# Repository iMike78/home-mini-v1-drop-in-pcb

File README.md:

# MiciMike drop-in PCB replacement for Google Home Mini (Gen 1)

[MiciMike Home Mini](https://github.com/iMike78/home-mini-v1-drop-in-pcb) is a drop-in PCB replacement for the original [Google Home Mini](https://en.wikipedia.org/wiki/Google_Nest_(smart_speakers)) with the Micro-USB power connector. It replaces the original electronics with open-source hardware based on an ESP32-S3 and an XMOS xCORE audio processor, and is intended to run ESPHome-based open voice assistant firmware.

The project follows the Home Assistant Voice Preview Edition architecture as closely as the Google Home Mini enclosure allows, while adapting the layout, connectors, controls, microphones, LEDs, and audio path to the original speaker shell.

## Current Status

- Schematic completed
- Component placement completed
- Routing completed
- Ground pour, shielding, and EMI strategy completed
- First prototype batch tested
- Validation batch received and under test
- ESPHome factory provisioning validated with BLE Improv and Home Assistant discovery

## Update: v0.9.5 Touch Controller Migration and Test Points

### Touch Controller Change

The ESP32-S3 built-in touch peripheral has been replaced with an external **MPR121 capacitive touch controller** on the I2C bus at address `0x5A`. This avoids an unresolved ESP-IDF / hardware issue (`IDFGH-16448`) where the touch sensor FSM could lock up and leave all channels stuck at their maximum raw value.

What changed:

- **Hardware:** MPR121 added on the clean `+3V3` rail. Touch pads connect through `ELEC0` to `ELEC2`; IRQ is on `GPIO2`. Unused electrodes are tied together to GND through a single 1 Mohm resistor.
- **Firmware:** the ESPHome `esp32_touch` component was removed and replaced with an `mpr121` hub plus three binary sensors for `volume_down`, `center_button`, and `volume_up`.
- **Freed pins:** ESP32-S3 `GPIO3` and `GPIO4` are no longer used for capacitive touch.

The center touch button is also used as the BLE Improv authorizer in the factory firmware, matching the Home Assistant Voice PE provisioning flow.

### New Solderable Test Points

The board exposes large, easy-to-solder test points for users who do not have the original Google Home Mini daughterboard and FPC connector, or who want to integrate the PCB into a custom enclosure.

- **+5V and GND power input pads:** allow direct power injection without using the original FPC connector.
- **Mute switch pad:** exposes the hardware mute input, which has an on-board pull-up. Pull this pad to GND to power the microphones; otherwise the board remains muted and the microphone path is disabled.

## ESPHome Firmware

The ESPHome configuration lives in [esphome/](./esphome/):

- [micimike-factory.yml](./esphome/micimike-factory.yml) is the manufacturing / first-install firmware. It mirrors the Home Assistant Voice PE factory flow: BLE Improv provisioning, center-button authorization, Home Assistant discovery, and the full voice firmware configuration included underneath.
- [micimike-voice.yml](./esphome/micimike-voice.yml) is the full voice assistant firmware configuration used by the factory build and by normal ESPHome installs.

Typical factory flashing:

```bash
esphome run esphome/micimike-factory.yml
```

After flashing, Home Assistant should discover the device via BLE Improv, ask for Wi-Fi credentials, request center-button authorization, and then add the ESPHome device. The fallback Wi-Fi AP is present, but no captive portal or web server is intentionally enabled.

## Crowdfunding

The crowdfunding campaign is live on Crowd Supply in its pre-order phase. You can subscribe there to show interest and receive email updates:

https://www.crowdsupply.com/micimike-rev-devices/micimike-home-mini-drop-in-pcb

If you are looking for a similar drop-in PCB replacement for the Google Nest Mini, see the sister project:

https://github.com/iMike78/nest-mini-drop-in-pcb

## Project Scope

This repository and its sister project are open-source hardware projects inspired in part by [Onju Voice](https://github.com/justLV/onju-voice), but designed around the open voice assistant hardware direction established by the Open Home Foundation and Home Assistant Voice Preview Edition.

The primary target audience is people who want to repurpose Google Home Mini and Google Nest Mini speakers into open-source Home Assistant voice assistant hardware and/or media player speaker output for [Music Assistant](https://www.music-assistant.io). The hardware may also be useful for other ESP32-based firmware projects.

The design integrates:

- ESP32-S3 for Wi-Fi, BLE, ESPHome, and onboard wake-word detection
- XMOS xCORE XU316 for advanced audio processing
- Local audio cleanup support for noise suppression, acoustic echo cancellation, interference cancellation, and automatic gain control

Functionally, the goal is to stay as compatible as practical with the [Home Assistant Voice Preview Edition](https://www.home-assistant.io/blog/2024/12/19/voice-preview-edition-the-era-of-open-voice/) reference design. The main differences come from the tight mechanical constraints of the Google Home Mini enclosure and original components.

This repository is not intended to become a separate upstream for new ESPHome or XMOS voice features. Feature development should generally happen upstream:

- https://github.com/esphome/home-assistant-voice-pe
- https://github.com/esphome/esphome
- https://github.com/esphome/voice-kit-xmos-firmware

## Collaboration and Contributions

If you would like to support the project, you can buy me a coffee via Ko-fi:

https://ko-fi.com/imike78

Contributions are especially welcome from people with board-level electrical design, KiCad layout, PCB routing, ground-pour strategy, EMI, and mixed-signal audio layout experience. Please open an issue, join an existing discussion, or start a new discussion in this repository.

Background discussion on the Home Assistant community forum:

https://community.home-assistant.io/t/any-news-on-alternative-to-onju-voice-pcb-repacement-design-for-google-nest-home-mini-speakers-with-added-xmos-chip-to-match-official-home-assistant-voice-preview-edition-reference-hardware/860001/

## Tools Used

- KiCad 9
- SnapEDA / LCSC for footprint sourcing

## Known Hardware Specifications

- 4-layer PCB
- ESP32-S3R8 bare chip with 16MB flash
- XMOS XU316-1024-QF60B-C24 xCORE DSP audio processor with 4MB flash
- Dual I2S buses for simultaneous audio input and output
- AIC3204 DAC and TPA6211 power amplifier for speaker output
- 2x T3902 MEMS microphones with 68mm spacing
- 4x SK6812 RGB LEDs
- MPR121 capacitive touch controller

## References

### Home Assistant Voice Preview Edition

- https://www.home-assistant.io/blog/2024/12/19/voice-preview-edition-the-era-of-open-voice/
- https://voice-pe.home-assistant.io/resources/
- https://support.nabucasa.com/hc/en-us/categories/24451727188125-Home-Assistant-Voice-Preview-Edition
- https://github.com/esphome/home-assistant-voice-pe
- https://esphome.github.io/home-assistant-voice-pe/

### XMOS xCORE DSP

- https://www.xmos.com/download/XU316-1024-QF60B-xcore.ai-Datasheet(3).pdf
- https://www.xmos.com/software-tools/
- https://www.xmos.com/develop/xcore-voice
- https://www.xmos.com/usb-multichannel-audio/
- https://www.xmos.com/xcore-ai

### XMOS Firmware

- https://github.com/esphome/voice-kit-xmos-firmware
- https://github.com/esphome/xmos_fwk_rtos
- https://github.com/esphome/xmos_fwk_io

## License

This project is licensed under the [CERN Open Hardware License Version 2 - Strongly Reciprocal (CERN-OHL-S v2)](./LICENCE).

Any modified version of this hardware must also be distributed under the same license.

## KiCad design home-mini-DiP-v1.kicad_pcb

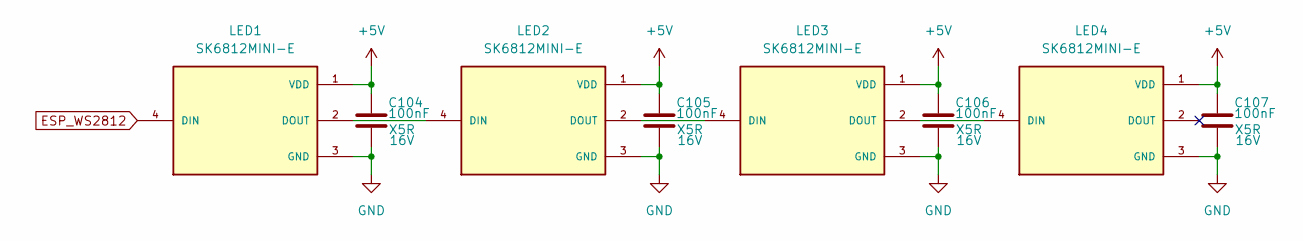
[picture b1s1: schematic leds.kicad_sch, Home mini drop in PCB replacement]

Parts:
C104, C105, C106, C107: 100nF; C_0402_1005Metric; Voltage 16V; Manufacturer Part CL05B104KO5NNNC; LCSC Part # C1525
LED1, LED2, LED3, LED4: SK6812MINI-E; Manufacturer Part SK6812MINI-E; LCSC Part # C5149201

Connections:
+5V: C104.1, C105.1, C106.1, C107.1, LED1.1 (VDD), LED2.1 (VDD), LED3.1 (VDD), LED4.1 (VDD); also elsewhere on the board
ESP_WS2812: LED1.4 (DIN); also elsewhere on the board
GND: C104.2, C105.2, C106.2, C107.2, LED1.3 (GND), LED2.3 (GND), LED3.3 (GND), LED4.3 (GND); also elsewhere on the board
unnamed: LED1.2 (DOUT), LED2.4 (DIN)
unnamed: LED2.2 (DOUT), LED3.4 (DIN)
unnamed: LED3.2 (DOUT), LED4.4 (DIN)

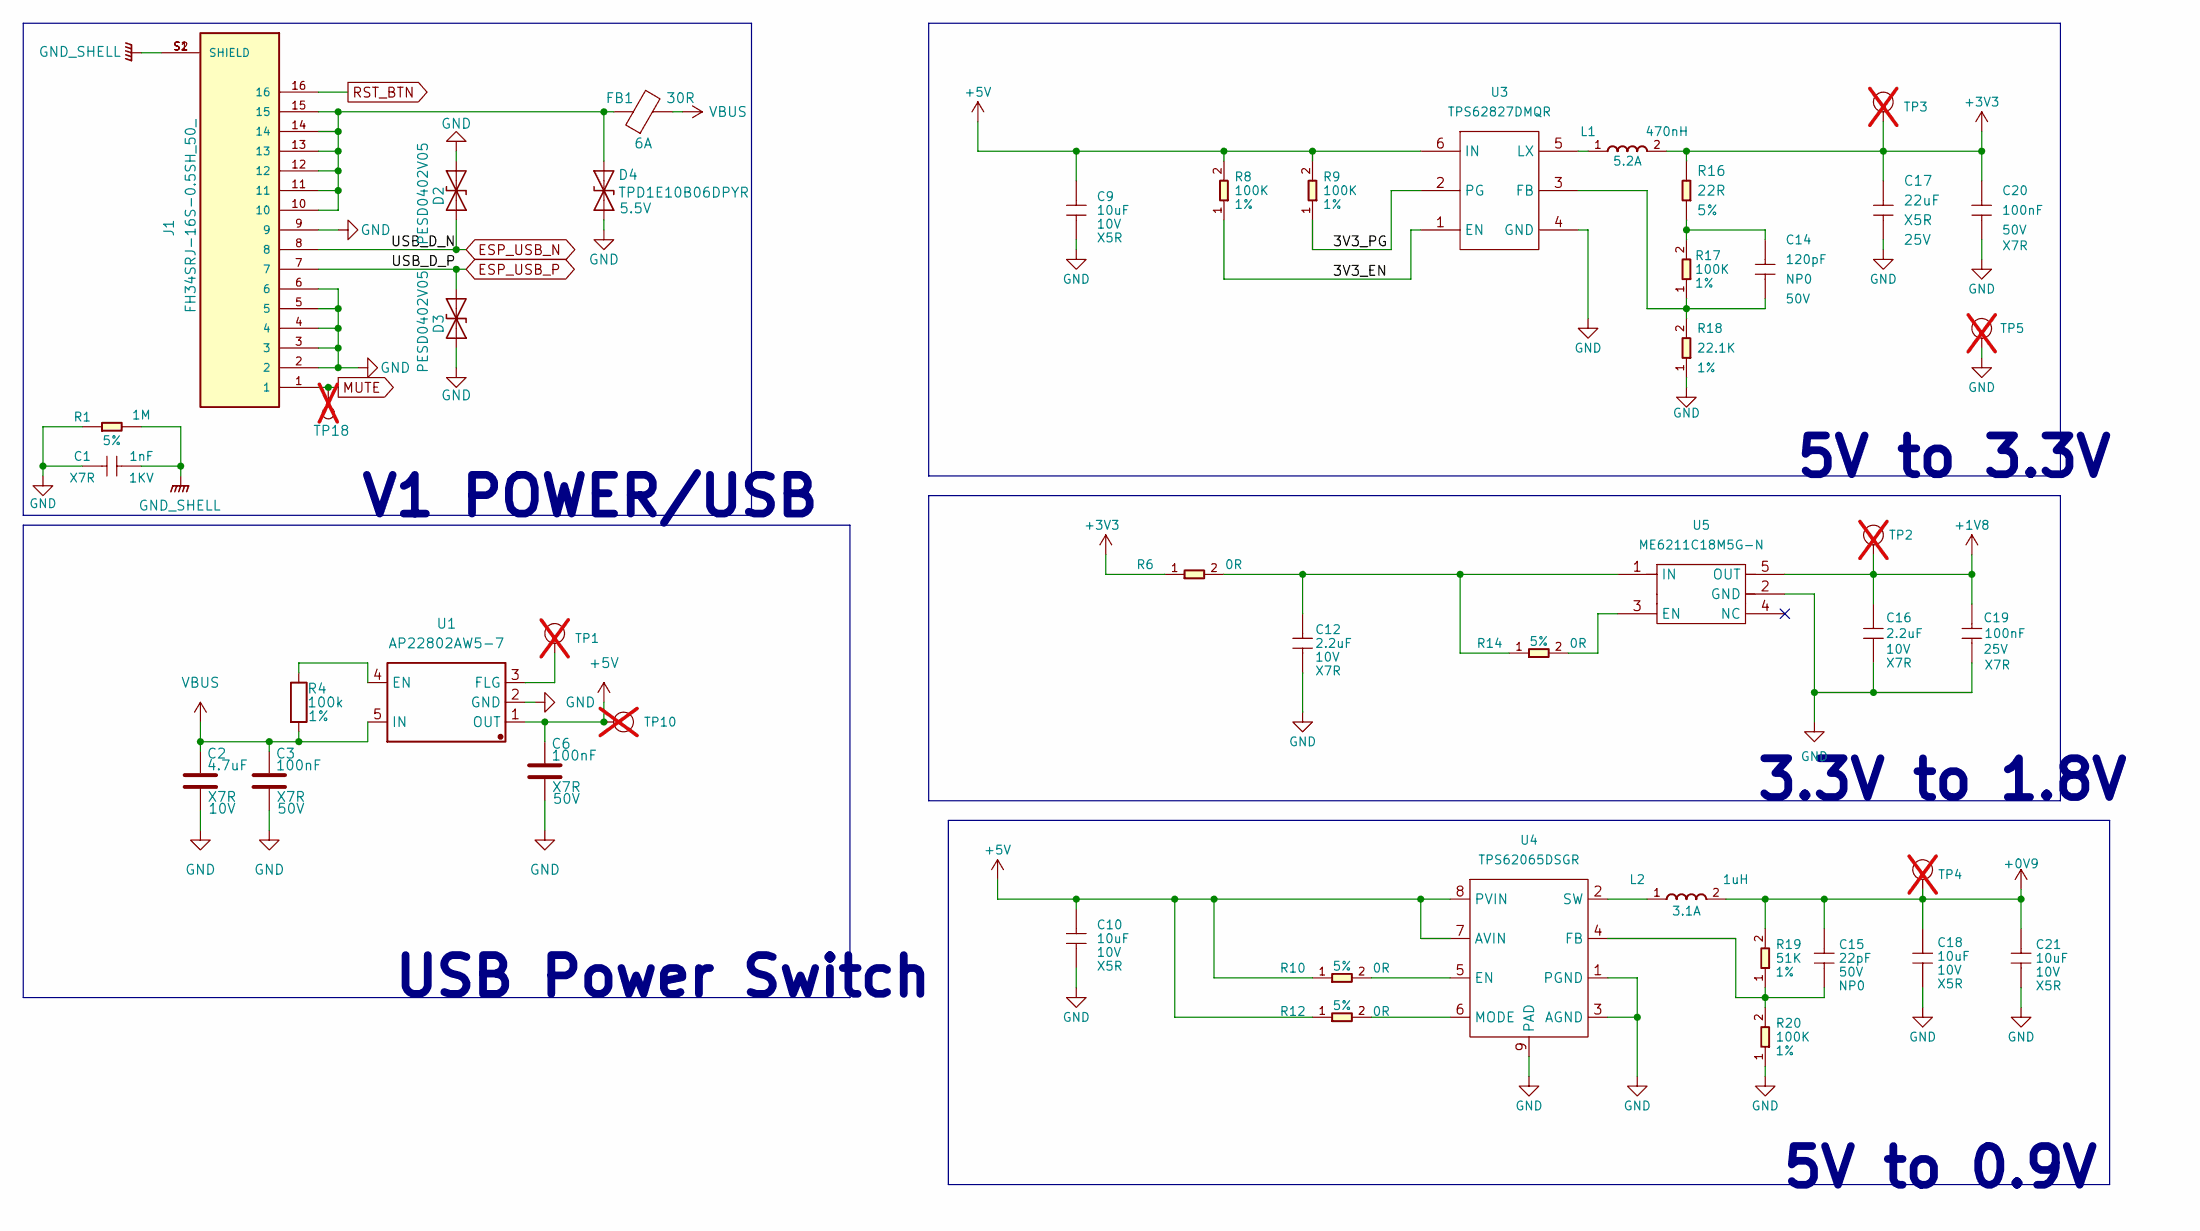
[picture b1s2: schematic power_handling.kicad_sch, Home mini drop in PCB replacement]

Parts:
C1: 1nF; C_1206_3216Metric; Voltage Rating 1KV; Voltage 2kV; MPN 1206B102K202NT; LCSC Part # C9196
C2: 4.7uF; C_0603_1608Metric; Voltage 10V; Manufacturer Part GRM188Z71A475KE15D; LCSC Part # C913474
C3, C6: 100nF; C_0603_1608Metric; Voltage 50V; Manufacturer Part CC0603KRX7R9BB104; LCSC Part # C14663
C9, C10, C18, C21: 10uF; C_0603_1608Metric; Voltage Rating 10V; Voltage 10V; MPN CL10A106KP8NNNC; LCSC Part # C19702
C12, C16: 2.2uF; C_0603_1608Metric; Voltage Rating 10V; Voltage 16V; MPN 0603B225K160NT; LCSC Part # C43922
C14: 120pF; C_0402_1005Metric; Voltage Rating 50V; Voltage 50V; MPN 0402CG121J500NT; LCSC Part # C40059
C15: 22pF; C_0402_1005Metric; Voltage Rating 50V; Voltage 50V; MPN 0402CG220J500NT; LCSC Part # C1555
C17: 22uF; C_0805_2012Metric; Voltage Rating 25V; Voltage 25V; MPN CL21A226MAQNNNE; LCSC Part # C45783
C19: 100nF; C_0402_1005Metric; Voltage Rating 25V; Voltage 16V; MPN CL05B104KO5NNNC; LCSC Part # C1525
C20: 100nF; C_0603_1608Metric; Voltage Rating 50V; Voltage 50V; MPN CC0603KRX7R9BB104; LCSC Part # C14663
D2, D3: PESD0402V05; D_0402_1005Metric; Manufacturer Part PESD0402V05; LCSC Part # C19626254
D4: TPD1E10B06DPYR; TPD1E05U06DPYR; Voltage 5.5V; Manufacturer Part TPD1E10B06DPYR; LCSC Part # C48260
FB1: 30R; BLM18PG300SN1D; Manufacturer Part BLM18PG300SN1D; LCSC Part # C17305
J1: FH34SRJ-16S-0.5SH_50_; HRS_FH34SRJ-16S-0.5SH_50_; Manufacturer Part FH34SRJ-16S-0.5SH(50); LCSC Part # C324725
L1: 470nH; L0806; Rating 5.2A; MPN WPN201610MR47MT; LCSC Part # C97014
L2: 1uH; L_Murata_DFE201610P; Rating 3.1A; MPN WPN201610U1R0MTY01; LCSC Part # C395545
R1: 1M; R_0805_2012Metric; Power Rating 5%; MPN RC0805JR-071ML; LCSC Part # C107699
R4: 100k; R_0402_1005Metric; Tolerance 1%; Manufacturer Part 0402WGJ0104TCE; LCSC Part # C25530
R6, R10, R12, R14: 0R; R_0402_1005Metric; Tolerance 5%; MPN 0402WGF0000TCE; LCSC Part # C17168
R8, R9, R17: 100K; R_0402_1005Metric; Power Rating 1%; MPN 0402WGJ0104TCE; LCSC Part # C25530
R16: 22R; R_0402_1005Metric; Power Rating 5%; MPN 0402WGF220JTCE; LCSC Part # C25092
R18: 22.1K; R_0402_1005Metric; Power Rating 1%; MPN 0402WGF2212TCE; LCSC Part # C43473
R19: 51K; R_0402_1005Metric; Tolerance 1%; MPN 0402WGF5102TCE; LCSC Part # C25794
R20: 100K; R_0402_1005Metric; Tolerance 1%; MPN 0402WGJ0104TCE; LCSC Part # C25530
TP1, TP2, TP3, TP4: TEST-POINT; TestPoint_Pad_D1.0mm; not fitted
TP5, TP10: TEST-POINT; TestPoint_Pad_D3.0mm; not fitted
TP18: MUTE; TestPoint_Pad_D1.0mm; not fitted
U1: AP22802AW5-7; SOT-23-5; Manufacturer Part AP22802AW5-7; LCSC Part # C211404
U3: TPS62827DMQR; DFN6-0.5-1.5X1.5X0.65MM; MPN TPS62827DMQR; LCSC Part # C2071448
U4: TPS62065DSGR; MPN TPS62065DSGR; LCSC Part # C398352
U5: ME6211C18M5G-N; SOT-23-5; MPN ME6211C18M5G-N; LCSC Part # C236671

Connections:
+0V9: C15.1, C18.1, C21.1, L2.2, R19.2, TP4.1 (T); also elsewhere on the board
+1V8: C16.1, C19.1, TP2.1 (T), U5.5 (OUT); also elsewhere on the board
+3V3: C17.1, C20.1, L1.2, R6.1, R16.2, TP3.1 (T); also elsewhere on the board
+5V: C6.1, C9.1, C10.1, R8.2, R9.2, R10.1, R12.1, TP10.1 (T), U1.1 (OUT), U3.6 (IN), U4.7 (AVIN), U4.8 (PVIN); also elsewhere on the board
/Power/3V3_EN: R8.1, U3.1 (EN)
/Power/3V3_PG: R9.1, U3.2 (PG)
ESP_USB_N: D2.2 (A2), J1.8; also elsewhere on the board
ESP_USB_P: D3.1 (A1), J1.7; also elsewhere on the board
GND: C1.1, C2.2, C3.2, C6.2, C9.2, C10.2, C12.2, C16.2, C17.2, C18.2, C19.2, C20.2, C21.2, D2.1 (A1), D3.2 (A2), D4.1 (A1), J1.2, J1.3, J1.4, J1.5, J1.6, J1.9, R1.1, R18.1, R20.1, TP5.1 (T), U1.2 (GND), U3.4 (GND), U4.1 (PGND), U4.3 (AGND), U4.9 (PAD), U5.2 (GND); also elsewhere on the board
GND_SHELL: C1.2, J1.S1 (SHIELD), J1.S2 (SHIELD), R1.2
MUTE: J1.1, TP18.1; also elsewhere on the board
unnamed: C14.1, R16.1, R17.2
unnamed: D4.2 (A2), FB1.1, J1.10, J1.11, J1.12, J1.13, J1.14, J1.15
unnamed: TP1.1 (T), U1.3 (FLG)
unnamed: R4.1, U1.4 (EN)
unnamed: C14.2, R17.1, R18.2, U3.3 (FB)
unnamed: L1.1, U3.5 (LX)
unnamed: R10.2, U4.5 (EN)
unnamed: C15.2, R19.1, R20.2, U4.4 (FB)
unnamed: R12.2, U4.6 (MODE)
unnamed: L2.1, U4.2 (SW)
unnamed: R14.2, U5.3 (EN)
unnamed: C12.1, R6.2, R14.1, U5.1 (IN)
RST_BTN: J1.16; also elsewhere on the board
VBUS: C2.1, C3.1, FB1.2, R4.2, U1.5 (IN); also elsewhere on the board

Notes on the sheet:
V1 POWER/USB
USB Power Switch
3.3V to 1.8V
5V to 3.3V
5V to 0.9V

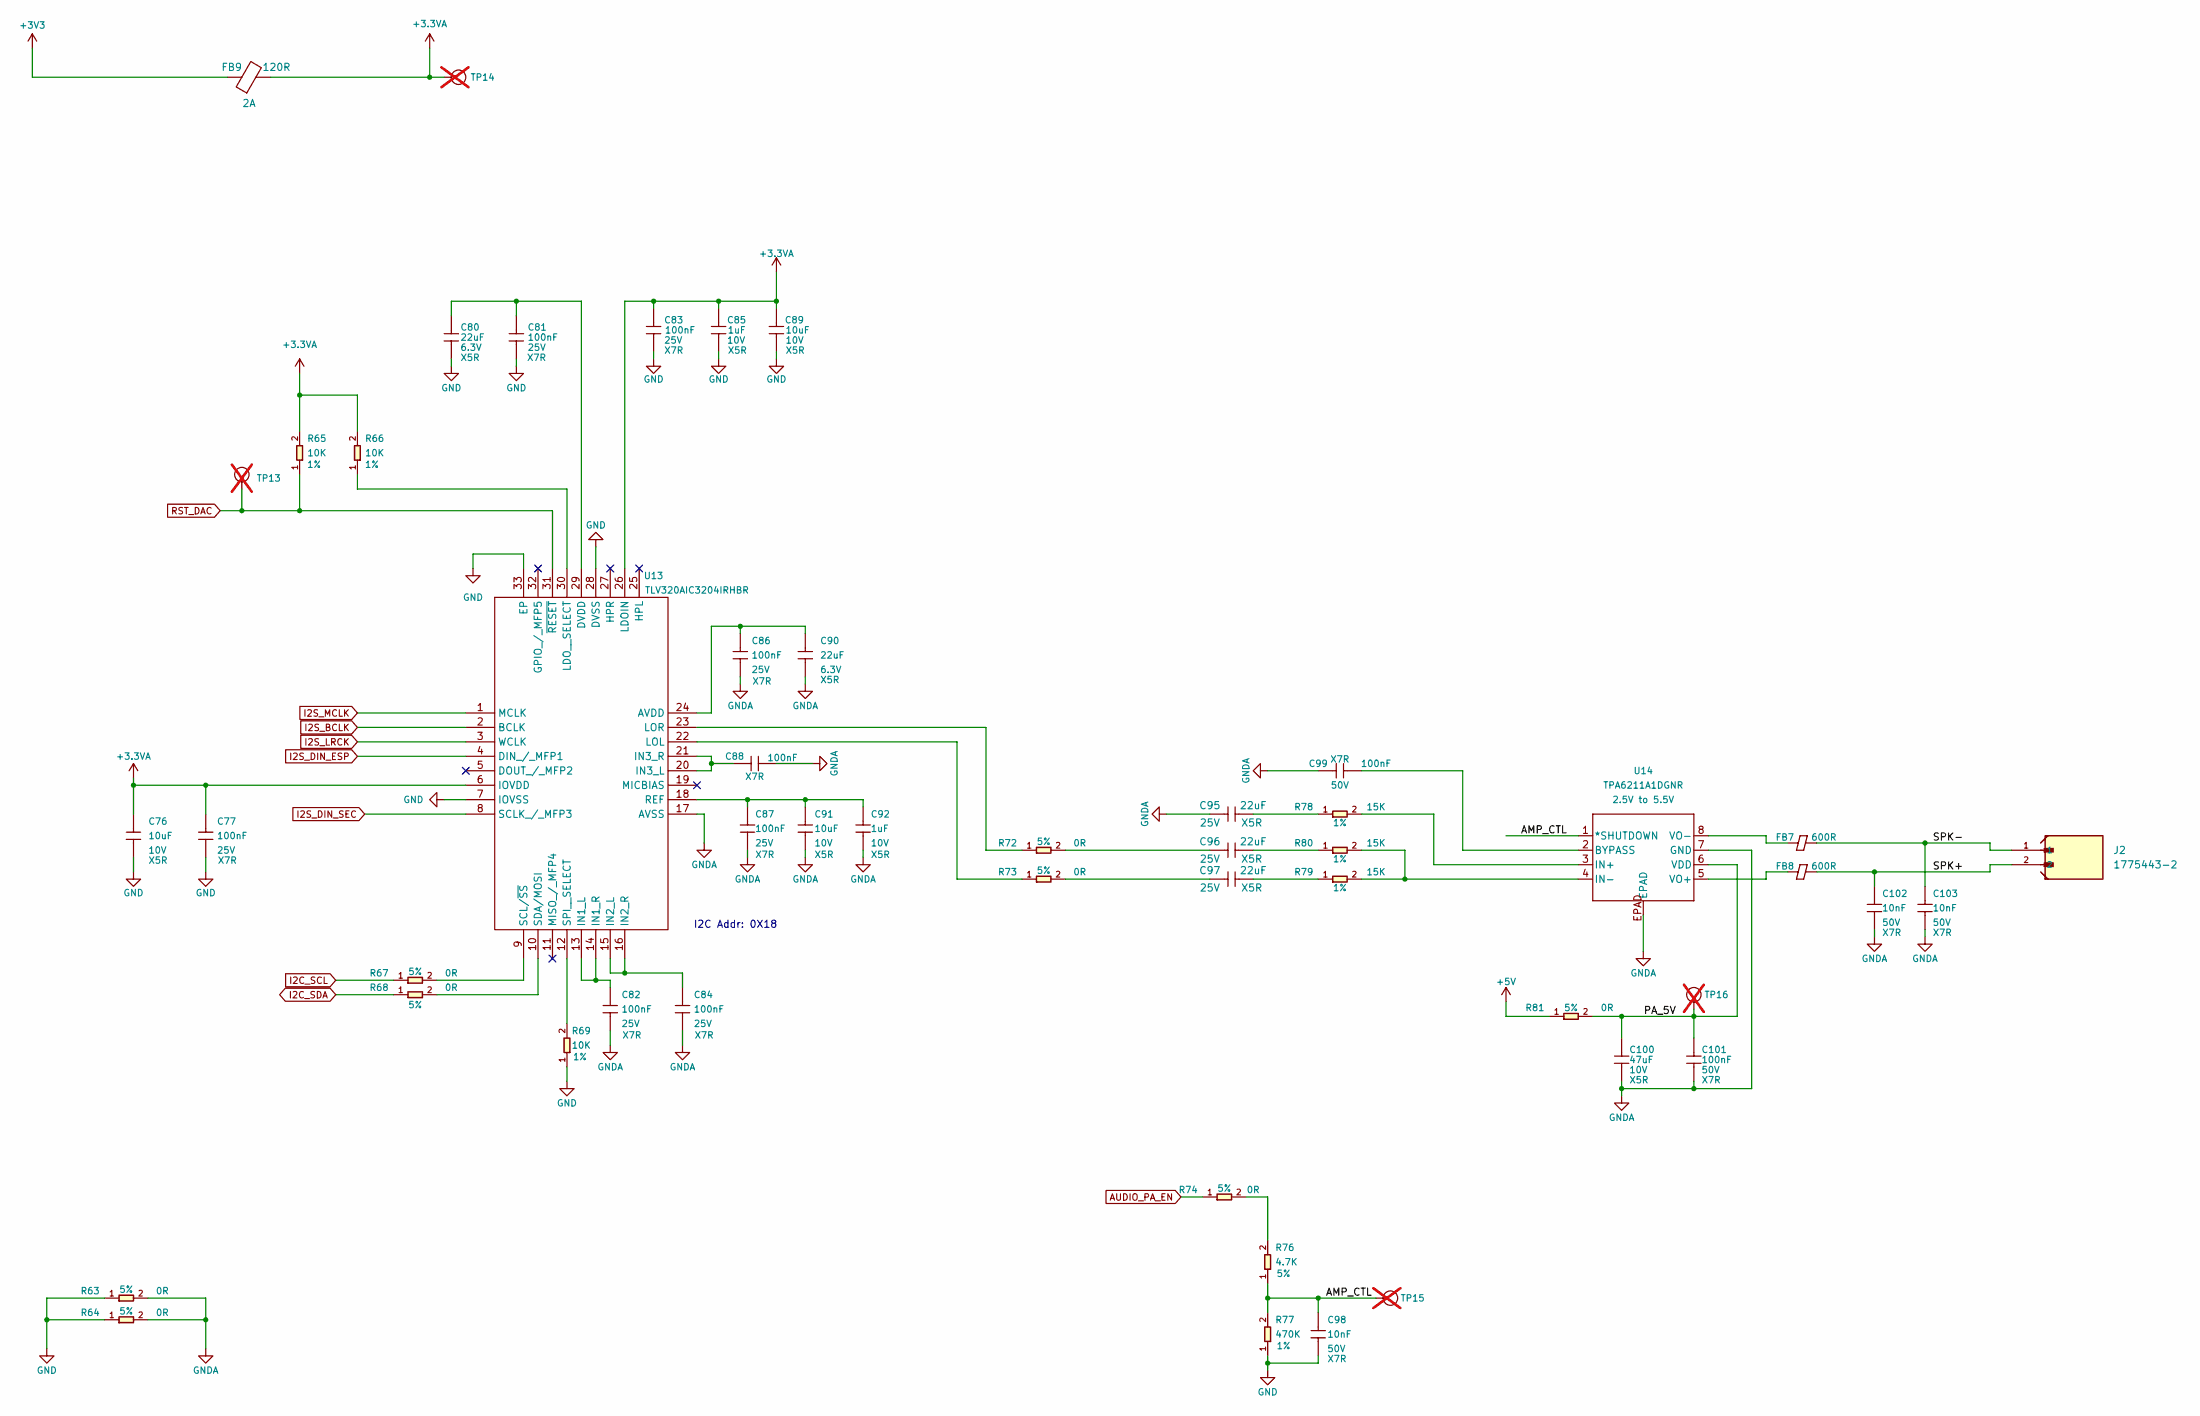
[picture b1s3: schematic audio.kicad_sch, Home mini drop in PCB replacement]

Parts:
C76, C89, C91: 10uF; C_0603_1608Metric; Voltage Rating 10V; Voltage 10V; MPN CL10A106KP8NNNC; LCSC Part # C19702
C77, C81, C82, C83, C84, C86, C87, C88: 100nF; C_0402_1005Metric; Voltage Rating 25V; Voltage 16V; MPN CL05B104KO5NNNC; LCSC Part # C1525
C80, C90: 22uF; C_0603_1608Metric; Voltage Rating 6.3V; Voltage 6.3V; MPN CL10A226MQ8NRNC; LCSC Part # C59461
C85, C92: 1uF; C_0402_1005Metric; Voltage Rating 10V; MPN CL05A105KA5NQNC; LCSC Part # C52923
C95, C96, C97: 22uF; C_0805_2012Metric; Voltage Rating 25V; Voltage 25V; MPN CL21A226MAQNNNE; LCSC Part # C45783
C98, C102, C103: 10nF; C_0402_1005Metric; Voltage Rating 50V; Voltage 50V; MPN CL05B103KB5NNNC; LCSC Part # C15195
C99, C101: 100nF; C_0603_1608Metric; Voltage Rating 50V; Voltage 50V; MPN CC0603KRX7R9BB104; LCSC Part # C14663
C100: 47uF; C_1206_3216Metric; Voltage Rating 10V; Voltage 10V; MPN CL31A476MPHNNNE; LCSC Part # C96123
FB7, FB8: 600R; BLM18PG121SN1D; Rating 500mA; MPN BLM18KG601SN1D; LCSC Part # C85833
FB9: 120R; BLM18PG121SN1D; Manufacturer Part BLM18PG121SN1D; LCSC Part # C14709
J2: 1775443-2; Manufacturer Part 1775443-2; LCSC Part # C5162845
R63, R64, R67, R68, R72, R73, R74: 0R; R_0402_1005Metric; Tolerance 5%; MPN 0402WGF0000TCE; LCSC Part # C17168
R65, R66, R69: 10K; R_0402_1005Metric; Tolerance 1%; MPN 0402WGF1002TCE; LCSC Part # C25744
R76: 4.7K; R_0402_1005Metric; Tolerance 5%; MPN 0402WGF4701TCE; LCSC Part # C25900
R77: 470K; R_0402_1005Metric; Tolerance 1%; Manufacturer Part 0402WGF4703TCE; LCSC Part # C25790
R78, R79, R80: 15K; R_0603_1608Metric; Tolerance 1%; Manufacturer Part 0603WAF1502T5E; LCSC Part # C22809
R81: 0R; R_0603_1608Metric; Tolerance 5%; Manufacturer Part 0603WAF0000T5E; LCSC Part # C21189
TP13, TP15: TEST-POINT; TestPoint_Pad_D1.0mm; not fitted
TP14, TP16: Test Point; TestPoint_Pad_D1.0mm; Part Type Test Point; not fitted
U13: TLV320AIC3204IRHBR; MPN TLV320AIC3204IRHBR; Mouser Part Number 595-V320AIC3204IRHBR
U14: TPA6211A1DGNR; Rating 2.5V to 5.5V; MPN TPA6211A1DGNR; LCSC Part # C7718

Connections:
+3.3VA: C76.1, C77.1, C83.1, C85.1, C89.1, FB9.2, R65.2, R66.2, TP14.1 (T), U13.6 (IOVDD), U13.26 (LDOIN)
+3V3: FB9.1; also elsewhere on the board
+5V: R81.1; also elsewhere on the board
/AUDIO/AMP_CTL: C98.1, R76.1, R77.2, TP15.1 (T), U14.1 (*SHUTDOWN)
/AUDIO/PA_5V: C100.1, C101.1, R81.2, TP16.1 (T), U14.6 (VDD)
/AUDIO/SPK+: C102.1, FB8.2, J2.2
/AUDIO/SPK-: C103.1, FB7.2, J2.1
AUDIO_PA_EN: R74.1; also elsewhere on the board
GND: C76.2, C77.2, C80.2, C81.2, C83.2, C85.2, C89.2, C98.2, R63.1, R64.1, R69.1, R77.1, U13.7 (IOVSS), U13.28 (DVSS), U13.33 (EP); also elsewhere on the board
GNDA: C82.2, C84.2, C86.2, C87.2, C88.2, C90.2, C91.2, C92.2, C95.1, C99.1, C100.2, C101.2, C102.2, C103.2, R63.2, R64.2, U13.17 (AVSS), U14.7 (GND), U14.EPAD
I2C_SCL: R67.1; also elsewhere on the board
I2C_SDA: R68.1; also elsewhere on the board
I2S_BCLK: U13.2 (BCLK); also elsewhere on the board
I2S_DIN_ESP: U13.4 (DIN_/_MFP1); also elsewhere on the board
I2S_DIN_SEC: U13.8 (SCLK_/_MFP3); also elsewhere on the board
I2S_LRCK: U13.3 (WCLK); also elsewhere on the board
I2S_MCLK: U13.1 (MCLK); also elsewhere on the board
unnamed: C95.2, R78.1
unnamed: C96.1, R72.2
unnamed: C96.2, R80.1
unnamed: C97.1, R73.2
unnamed: C97.2, R79.1
unnamed: R74.2, R76.2
unnamed: C86.1, C90.1, U13.24 (AVDD)
unnamed: C80.1, C81.1, U13.29 (DVDD)
unnamed: C82.1, U13.13 (IN1_L), U13.14 (IN1_R)
unnamed: C84.1, U13.15 (IN2_L), U13.16 (IN2_R)
unnamed: C88.1, U13.20 (IN3_L), U13.21 (IN3_R)
unnamed: R66.1, U13.30 (LDO__SELECT)
unnamed: R73.1, U13.22 (LOL)
unnamed: R72.1, U13.23 (LOR)
unnamed: C87.1, C91.1, C92.1, U13.18 (REF)
unnamed: R67.2, U13.9 (SCL/~SS)
unnamed: R68.2, U13.10 (SDA/MOSI)
unnamed: R69.2, U13.12 (SPI__SELECT)
unnamed: C99.2, U14.2 (BYPASS)
unnamed: R78.2, U14.3 (IN+)
unnamed: R79.2, R80.2, U14.4 (IN-)
unnamed: FB8.1, U14.5 (VO+)
unnamed: FB7.1, U14.8 (VO-)
RST_DAC: R65.1, TP13.1 (T), U13.31 (~RESET); also elsewhere on the board

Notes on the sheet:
I2C Addr: 0X18

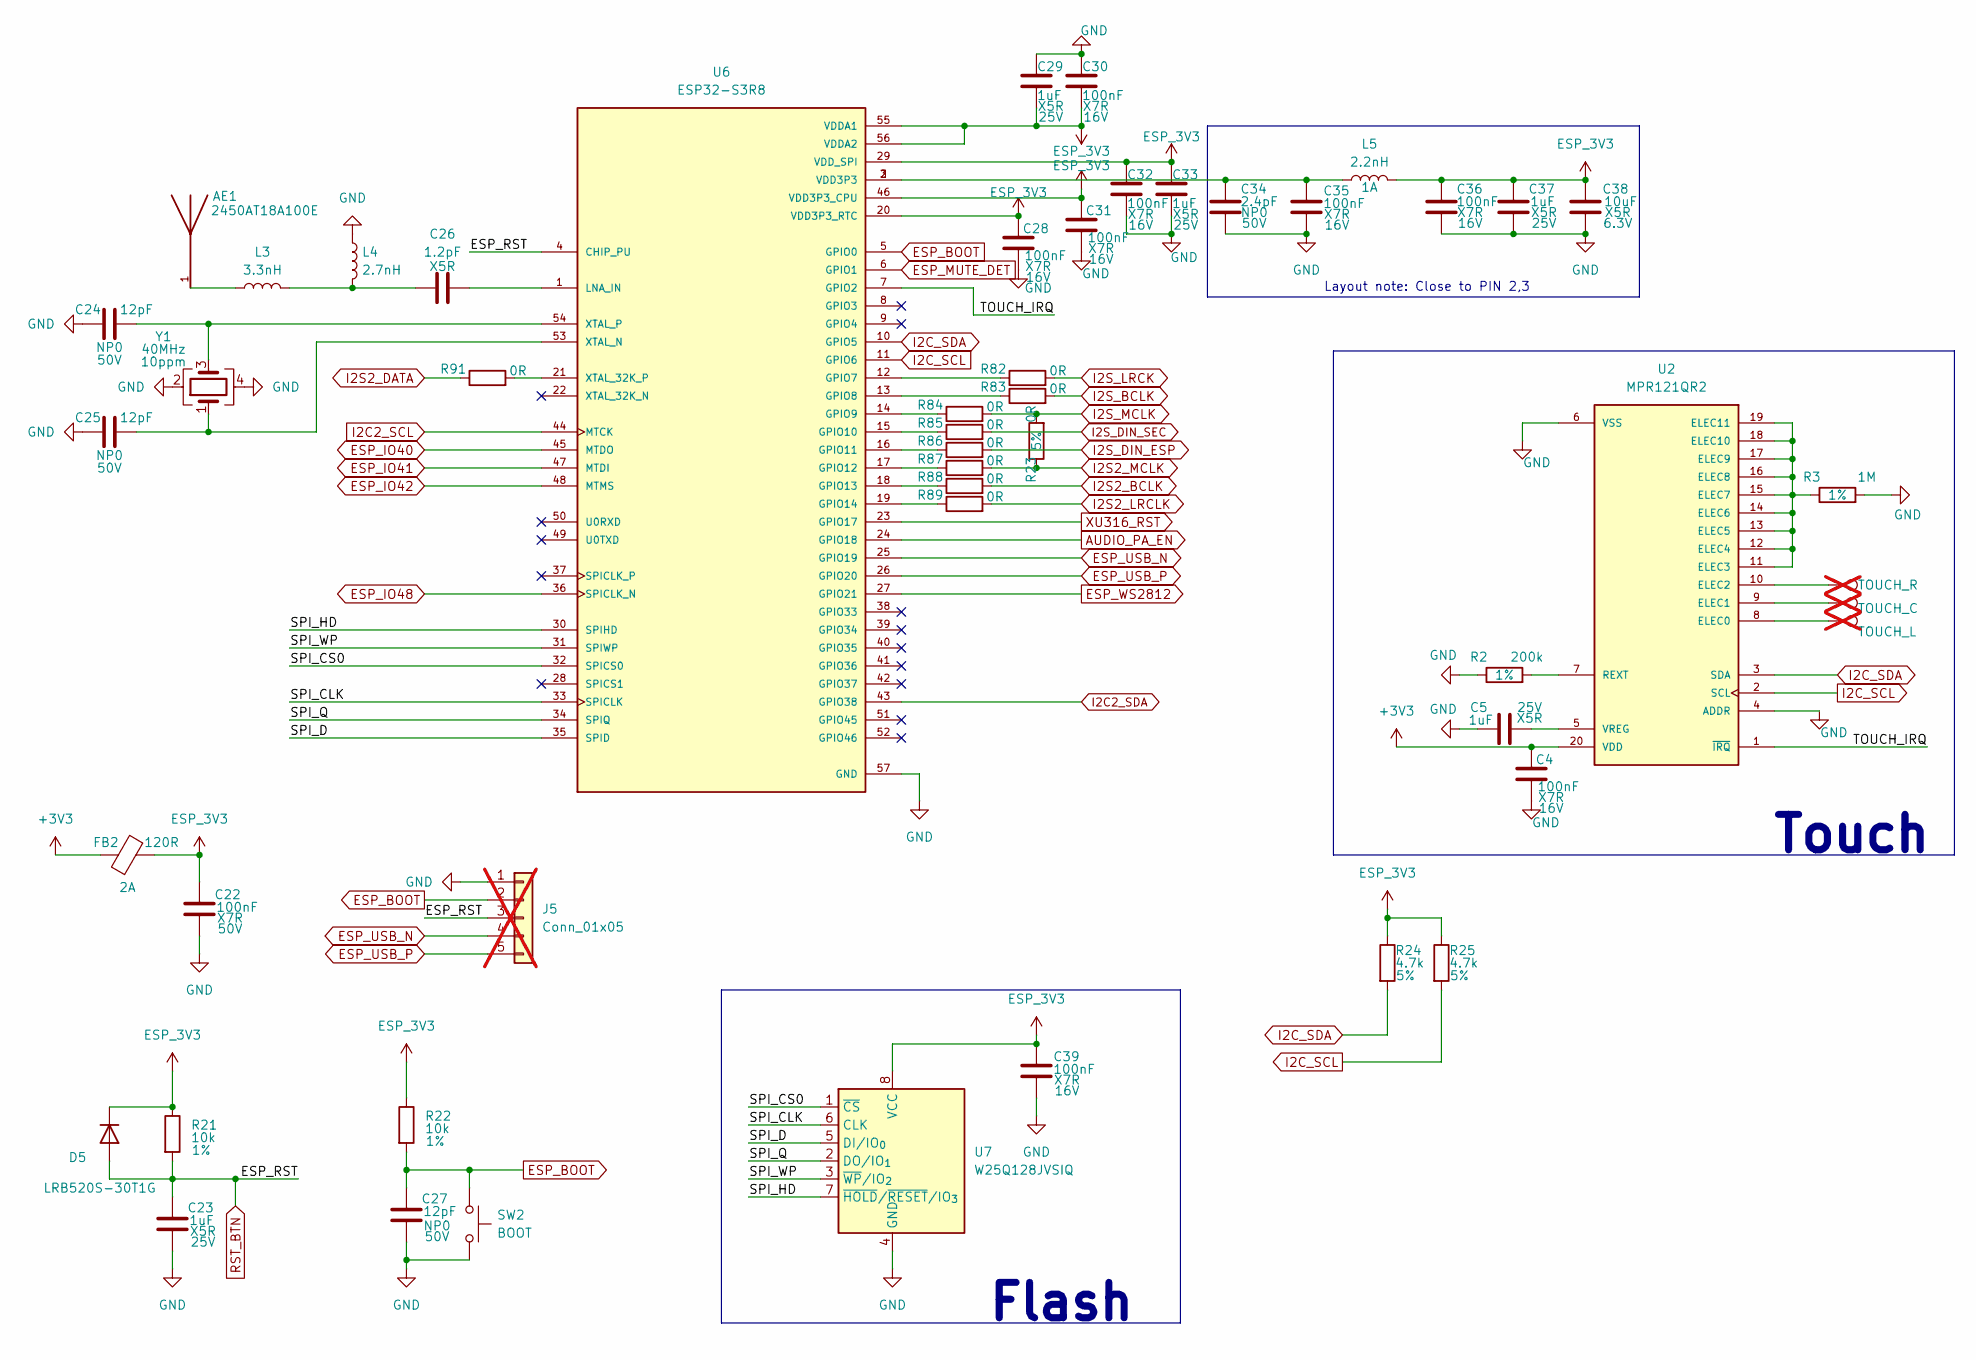
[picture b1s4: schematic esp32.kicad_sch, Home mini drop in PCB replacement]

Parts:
AE1: 2450AT18A100E; Johanson_2450AT18x100; Manufacturer Part 2450AT18A100E; LCSC Part # C89334
C4, C28, C30, C31, C32, C35, C36, C39: 100nF; C_0402_1005Metric; Voltage 16V; Manufacturer Part CL05B104KO5NNNC; LCSC Part # C1525
C5, C23, C29, C33, C37: 1uF; C_0402_1005Metric; Voltage 25V; Manufacturer Part CL05A105KA5NQNC; LCSC Part # C52923
C22: 100nF; C_0603_1608Metric; Voltage 50V; Manufacturer Part CC0603KRX7R9BB104; LCSC Part # C14663
C24, C25, C27: 12pF; C_0402_1005Metric; Voltage 50V; Manufacturer Part 0402CG120J500NT; LCSC Part # C1547
C26: 1.2pF; C_0402_1005Metric; Voltage 10V; Manufacturer Part CC0402BRNPO9BN1R2; LCSC Part # C327292
C34: 2.4pF; C_0402_1005Metric; Voltage 50V; Manufacturer Part 0402CG2R4C500NT; LCSC Part # C48346
C38: 10uF; C_0402_1005Metric; Voltage 6.3V; Manufacturer Part CL05A106MQ5NUNC; LCSC Part # C15525
D5: LRB520S-30T1G; D_SOD-523; Manufacturer Part LRB520S-30T1G; LCSC Part # C83680
FB2: 120R; BLM18PG121SN1D; Manufacturer Part BLM18PG121SN1D; LCSC Part # C14709
J5: Conn_01x05; PinHeader_1x05_P2.54mm_Vertical; not fitted
L3: 3.3nH; L_0402_1005Metric; Manufacturer Part SDCL1005C3N3STDF; LCSC Part # C16526
L4: 2.7nH; L_0402_1005Metric; Manufacturer Part MHQ1005P2N7BT000; LCSC Part # C434826
L5: 2.2nH; L_0402_1005Metric; Manufacturer Part LQG15HS2N2B02D; LCSC Part # C162540
R2: 200k; R_0402_1005Metric; Tolerance 1%; MPN 0402WGF2003TCE; LCSC Part # C25764
R3: 1M; R_0402_1005Metric; Tolerance 1%; MPN 0402WGJ0105TCE; LCSC Part # C26087
R21, R22: 10k; R_0402_1005Metric; Tolerance 1%; Manufacturer Part 0402WGF1002TCE; LCSC Part # C25744
R23, R82, R83, R84, R85, R86, R87, R88, R89, R91: 0R; R_0402_1005Metric; Tolerance 5%; Manufacturer Part 0402WGF0000TCE; LCSC Part # C17168
R24, R25: 4.7k; R_0402_1005Metric; Tolerance 5%; Manufacturer Part 0402WGF4701TCE; LCSC Part # C25900
SW2: BOOT; SW-SMD_4P-L4.2-W3.2-P2.15-LS4.5; Manufacturer Part PTS810SJS250SMTRLFS; LCSC Part # C221897
TP6: TOUCH_L; TestPoint_Pad_2.5x2.5mm; not fitted
TP7: TOUCH_C; TestPoint_Pad_2.5x2.5mm; not fitted
TP8: TOUCH_R; TestPoint_Pad_2.5x2.5mm; not fitted
U2: MPR121QR2; MPN MPR121QR2; LCSC Part # C91322
U6: ESP32-S3R8; QFN40P700X700X90-57N; Manufacturer Part ESP32-S3R8; LCSC Part # C2913194
U7: W25Q128JVSIQ; SOIC-8_5.3x5.3mm_P1.27mm; Manufacturer Part W25Q128JVSIQ; LCSC Part # C97521
Y1: 40MHz; Crystal_SMD_2016-4Pin_2.0x1.6mm; Tolerance 10ppm; Manufacturer Part TAXM40M4ZCBCDT2T; LCSC Part # C424431

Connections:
+3V3: C4.1, FB2.1, U2.20 (VDD); also elsewhere on the board
/ESP32-S3R8/SPI_CLK: U6.33 (SPICLK), U7.6 (CLK)
/ESP32-S3R8/SPI_CS0: U6.32 (SPICS0), U7.1 (~CS)
/ESP32-S3R8/SPI_D: U6.35 (SPID), U7.5 (DI/IO_{0})
/ESP32-S3R8/SPI_HD: U6.30 (SPIHD), U7.7 (~HOLD/~RESET/IO_{3})
/ESP32-S3R8/SPI_Q: U6.34 (SPIQ), U7.2 (DO/IO_{1})
/ESP32-S3R8/SPI_WP: U6.31 (SPIWP), U7.3 (~WP/IO_{2})
/ESP32-S3R8/TOUCH_IRQ: U2.1 (~IRQ), U6.7 (GPIO2)
AUDIO_PA_EN: U6.24 (GPIO18); also elsewhere on the board
ESP_3V3: C22.1, C28.1, C29.2, C30.2, C31.1, C32.1, C33.1, C36.1, C37.1, C38.1, C39.1, D5.1 (K), FB2.2, L5.2, R21.1, R22.1, R24.1, R25.1, U6.20 (VDD3P3_RTC), U6.29 (VDD_SPI), U6.46 (VDD3P3_CPU), U6.55 (VDDA1), U6.56 (VDDA2), U7.8 (VCC); also elsewhere on the board
ESP_BOOT: C27.1, J5.2, R22.2, SW2.1, U6.5 (GPIO0)
ESP_IO40: U6.45 (MTDO); also elsewhere on the board
ESP_IO41: U6.47 (MTDI); also elsewhere on the board
ESP_IO42: U6.48 (MTMS)
ESP_IO48: U6.36 (SPICLK_N)
ESP_MUTE_DET: U6.6 (GPIO1); also elsewhere on the board
ESP_USB_N: J5.4, U6.25 (GPIO19); also elsewhere on the board
ESP_USB_P: J5.5, U6.26 (GPIO20); also elsewhere on the board
ESP_WS2812: U6.27 (GPIO21); also elsewhere on the board
GND: C4.2, C5.1, C22.2, C23.2, C24.1, C25.1, C27.2, C28.2, C29.1, C30.1, C31.2, C32.2, C33.2, C34.2, C35.2, C36.2, C37.2, C38.2, C39.2, J5.1, L4.1, R2.1, R3.2, SW2.2, U2.4 (ADDR), U2.6 (VSS), U6.57 (GND), U7.4 (GND), Y1.2, Y1.4; also elsewhere on the board
I2C2_SCL: U6.44 (MTCK); also elsewhere on the board
I2C2_SDA: U6.43 (GPIO38); also elsewhere on the board
I2C_SCL: R25.2, U2.2 (SCL), U6.11 (GPIO6); also elsewhere on the board
I2C_SDA: R24.2, U2.3 (SDA), U6.10 (GPIO5); also elsewhere on the board
I2S2_BCLK: R88.2; also elsewhere on the board
I2S2_DATA: R91.1; also elsewhere on the board
I2S2_LRCLK: R89.2; also elsewhere on the board
I2S2_MCLK: R23.1, R87.2; also elsewhere on the board
I2S_BCLK: R83.2; also elsewhere on the board
I2S_DIN_ESP: R86.2; also elsewhere on the board
I2S_DIN_SEC: R85.2; also elsewhere on the board
I2S_LRCK: R82.2; also elsewhere on the board
I2S_MCLK: R23.2, R84.2; also elsewhere on the board
unnamed: AE1.1, L3.1
unnamed: C26.1, L3.2, L4.2
unnamed: C34.1, C35.1, L5.1, U6.2 (VDD3P3), U6.3 (VDD3P3)
unnamed: TP6.1, U2.8 (ELEC0)
unnamed: TP7.1, U2.9 (ELEC1)
unnamed: TP8.1, U2.10 (ELEC2)
unnamed: R3.1, U2.11 (ELEC3), U2.12 (ELEC4), U2.13 (ELEC5), U2.14 (ELEC6), U2.15 (ELEC7), U2.16 (ELEC8), U2.17 (ELEC9), U2.18 (ELEC10), U2.19 (ELEC11)
unnamed: R2.2, U2.7 (REXT)
unnamed: C5.2, U2.5 (VREG)
unnamed: R82.1, U6.12 (GPIO7)
unnamed: R83.1, U6.13 (GPIO8)
unnamed: R84.1, U6.14 (GPIO9)
unnamed: R85.1, U6.15 (GPIO10)
unnamed: R86.1, U6.16 (GPIO11)
unnamed: R87.1, U6.17 (GPIO12)
unnamed: R88.1, U6.18 (GPIO13)
unnamed: R89.1, U6.19 (GPIO14)
unnamed: C26.2, U6.1 (LNA_IN)
unnamed: R91.2, U6.21 (XTAL_32K_P)
unnamed: C25.2, U6.53 (XTAL_N), Y1.1
unnamed: C24.2, U6.54 (XTAL_P), Y1.3
RST_BTN: C23.1, D5.2 (A), J5.3, R21.2, U6.4 (CHIP_PU); also elsewhere on the board
XU316_RST: U6.23 (GPIO17); also elsewhere on the board

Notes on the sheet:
Flash
Touch
Layout note: Close to PIN 2,3

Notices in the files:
home-mini-DiP-v1.kicad_pcb:
CERN-OHL-S-2.0
